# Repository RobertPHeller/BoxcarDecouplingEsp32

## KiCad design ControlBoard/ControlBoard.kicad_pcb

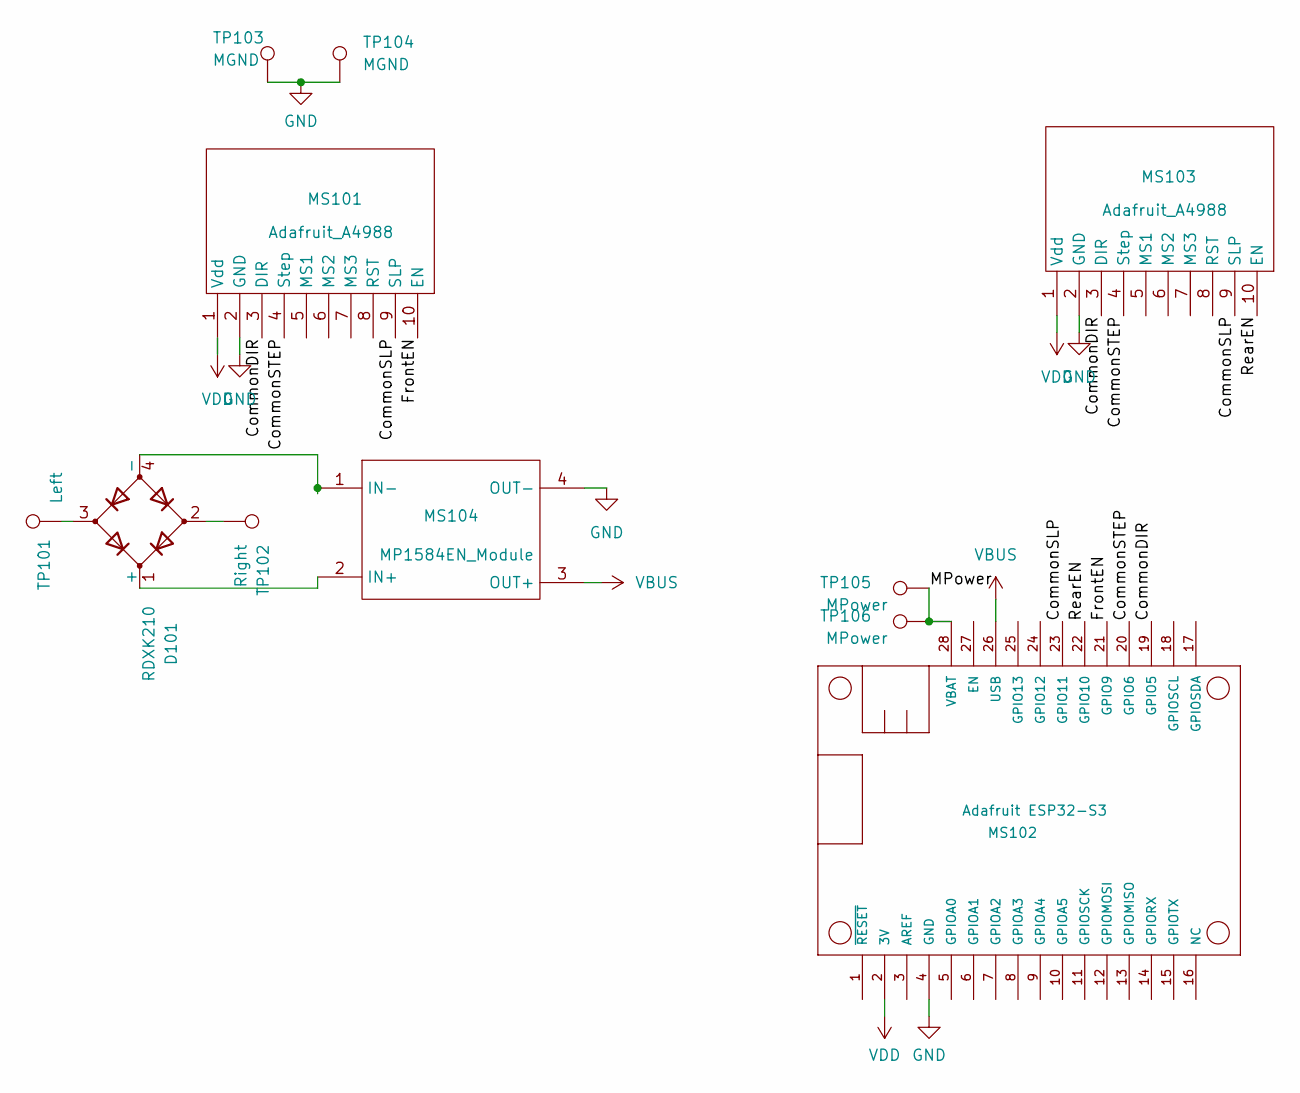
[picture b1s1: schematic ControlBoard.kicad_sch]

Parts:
D101: RDXK210; DXK310_T0_00001
MS101, MS103: Adafruit_A4988; Adafruit A4988
MS102: Adafruit ESP32-S3; FEATHERWING
MS104: MP1584EN_Module; MP1584EN Module
TP101: Left; TestPoint_Pad_4.0x4.0mm
TP102: Right; TestPoint_Pad_4.0x4.0mm
TP103, TP104: MGND; TestPoint_Pad_4.0x4.0mm
TP105, TP106: MPower; TestPoint_Pad_4.0x4.0mm

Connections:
/CommonDIR: MS101.3 (DIR), MS102.19 (GPIO5), MS103.3 (DIR)
/CommonSLP: MS101.9 (SLP), MS102.23 (GPIO11), MS103.9 (SLP)
/CommonSTEP: MS101.4 (Step), MS102.20 (GPIO6), MS103.4 (Step)
/FrontEN: MS101.10 (EN), MS102.21 (GPIO9)
/MPower: MS102.28 (VBAT), TP105.1, TP106.1
/RearEN: MS102.22 (GPIO10), MS103.10 (EN)
GND: MS101.2 (GND), MS102.4 (GND), MS103.2 (GND), MS104.4 (OUT-), TP103.1, TP104.1
unnamed: D101.1 (+), MS104.2 (IN+)
unnamed: D101.2, TP102.1
unnamed: D101.3, TP101.1
unnamed: D101.4 (-), MS104.1 (IN-)
VBUS: MS102.26 (USB), MS104.3 (OUT+)
VDD: MS101.1 (Vdd), MS102.2 (3V), MS103.1 (Vdd)

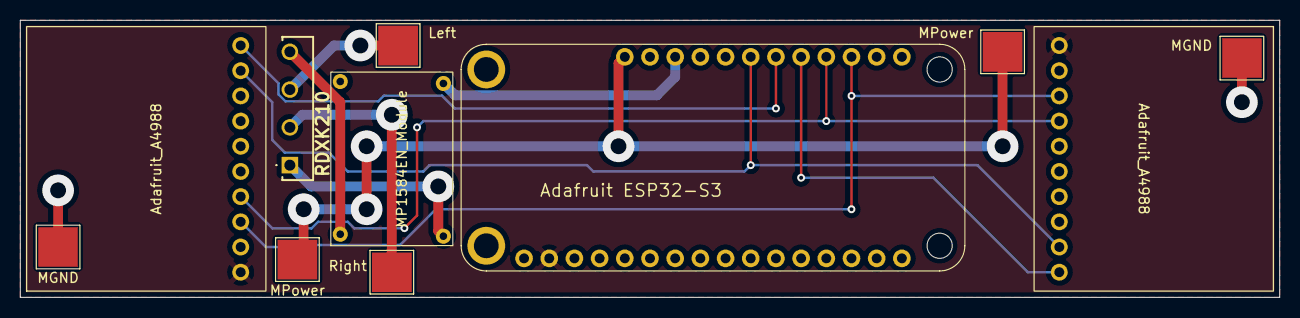
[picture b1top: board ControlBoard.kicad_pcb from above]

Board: 2 copper layers, 127.0 x 27.9 mm, 11 parts (0 on the bottom side), 13 nets.

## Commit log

2025-10-30 Add Sleep. Start on the firmware.
2025-10-30 Add WiFi boilerplate.
2025-10-30 Add Fritzing breadboard.
2025-10-31 Add WiFi and start UDP in firmware. Add 3D models to the PCB.
2025-11-01 Add Schematic PDF and 3D views of PCB.
2025-11-01 Completed LCC firmware. Split off LocoFi firmware.
2025-11-05 Completed first draft of the firmware.
2025-11-11 Snapshot commit.
